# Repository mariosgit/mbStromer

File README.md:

# mbStromer

The Asymmetric Power Supply for Eurorack.

Provides up to 50W, oldschool linear regulator stuff (low noise), for use with a transformer (2x12V 50VA)

With heatsink: 50W
* 12V 3A
* -12V 1A

Without heatsink 25W
* 12V ~1.5A
* -12V ~0.5A

## Status

Under testing, minor fixes pending...

## Mounting

The board can be mounted on a heatsink or directly onto the metal case back, which then becomes the heatsink. You will need 2 silicone pads and 2 Alu/Copper distance peaces 30x40mm. Use the center screw holes to minimize stress on the pcb.

When used without heatsink, put it on distancers so air can circulate around the board which is designed to be disipate a little heat as well.

### Bugs (beta)

* 7912 has no ground conn ! patch it.

## Todo

* Add 5V option ? No one uses it anyway !? Disturbs fend-shui of the layout :-P

## License

#### Attribution-NonCommercial-ShareAlike - CC BY-NC-SA 

```
Attribution — You must give appropriate credit, provide a link to the license, and indicate if changes were made. You may do so in any reasonable manner, but not in any way that suggests the licensor endorses you or your use.

NonCommercial — You may not use the material for commercial purposes.

ShareAlike — If you remix, transform, or build upon the material, you must distribute your contributions under the same license as the original.

No additional restrictions — You may not apply legal terms or technological measures that legally restrict others from doing anything the license permits.
```
[All the legal blabla here](https://creativecommons.org/licenses/by-nc-sa/4.0/legalcode)

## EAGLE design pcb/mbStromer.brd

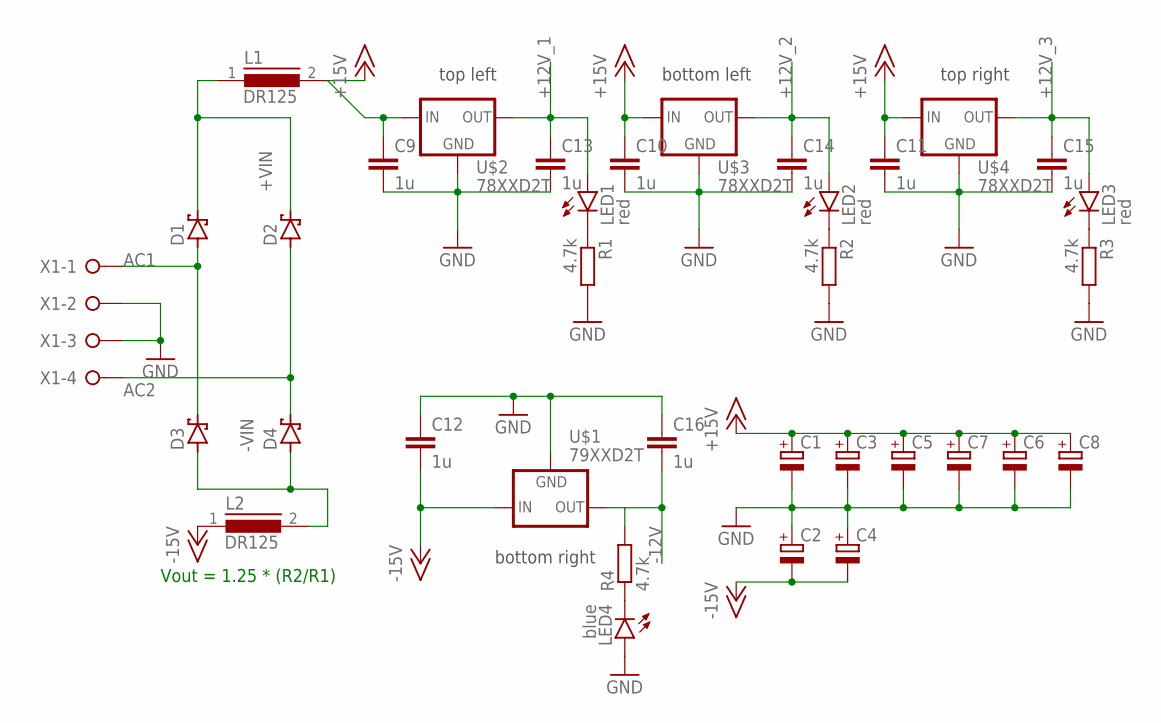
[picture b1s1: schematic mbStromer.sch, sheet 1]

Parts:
C1, C2, C3, C4, C5, C6, C7, C8: CPOL-EU150CLZ-1014; 150CLZ-1014
C9, C10, C11, C12, C13, C14, C15, C16: 1u; C1206K
D1, D2, D3, D4: SCHOTTKY-DIODESMC; SMC
L1, L2: DR125
LED1, LED2, LED3: red; CHIPLED_1206
LED4: blue; CHIPLED_1206
R1, R2, R3, R4: 4.7k; R1206
U$1: 79XXD2T; D2PACK
U$2, U$3, U$4: 78XXD2T; D2PACK
X1: W237-04P; W237-4P

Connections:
+12V_1: C13.1, LED1.A, U$2.3 (OUT); also elsewhere on the board
+12V_2: C14.1, LED2.A, U$3.3 (OUT); also elsewhere on the board
+12V_3: C15.1, LED3.A, U$4.3 (OUT); also elsewhere on the board
+15V: C1.+, C3.+, C5.+, C6.+, C7.+, C8.+, C9.1, C10.1, C11.1, L1.2, U$2.1 (IN), U$3.1 (IN), U$4.1 (IN)
+VIN: D1.C, D2.C, L1.1
-12V: C16.2, R4.2, U$1.3 (OUT); also elsewhere on the board
-15V: C2.-, C4.-, C12.2, L2.1, U$1.2 (IN)
-VIN: D3.A, D4.A, L2.2
AC1: D1.A, D3.C, X1.1
AC2: D2.A, D4.C, X1.4
GND: C1.-, C2.+, C3.-, C4.+, C5.-, C6.-, C7.-, C8.-, C9.2, C10.2, C11.2, C12.1, C13.2, C14.2, C15.2, C16.1, LED4.A, R1.2, R2.2, R3.2, U$1.1 (GND), U$2.2 (GND), U$3.2 (GND), U$4.2 (GND), X1.2, X1.3; also elsewhere on the board
unnamed: LED1.C, R1.1
unnamed: LED2.C, R2.1
unnamed: LED3.C, R3.1
unnamed: LED4.C, R4.1

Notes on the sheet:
Vout = 1.25 * (R2/R1)
top right
top left
bottom left
bottom right

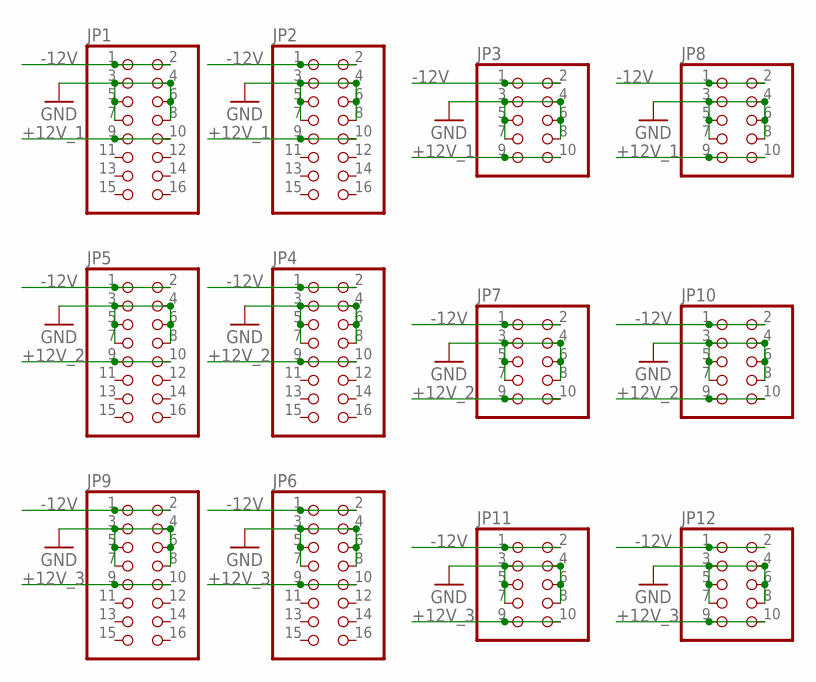
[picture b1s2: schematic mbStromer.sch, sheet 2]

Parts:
JP1, JP2, JP4, JP5, JP6, JP9: PINHD-2X8/90; 2X08/90
JP3, JP7, JP8, JP10, JP11, JP12: PINHD-2X5/90; 2X05/90

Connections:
+12V_1: JP1.9, JP1.10, JP2.9, JP2.10, JP3.9, JP3.10, JP8.9, JP8.10; also elsewhere on the board
+12V_2: JP4.9, JP4.10, JP5.9, JP5.10, JP7.9, JP7.10, JP10.9, JP10.10; also elsewhere on the board
+12V_3: JP6.9, JP6.10, JP9.9, JP9.10, JP11.9, JP11.10, JP12.9, JP12.10; also elsewhere on the board
-12V: JP1.1, JP1.2, JP2.1, JP2.2, JP3.1, JP3.2, JP4.1, JP4.2, JP5.1, JP5.2, JP6.1, JP6.2, JP7.1, JP7.2, JP8.1, JP8.2, JP9.1, JP9.2, JP10.1, JP10.2, JP11.1, JP11.2, JP12.1, JP12.2; also elsewhere on the board
GND: JP1.3, JP1.4, JP1.5, JP1.6, JP1.7, JP1.8, JP2.3, JP2.4, JP2.5, JP2.6, JP2.7, JP2.8, JP3.3, JP3.4, JP3.5, JP3.6, JP3.7, JP3.8, JP4.3, JP4.4, JP4.5, JP4.6, JP4.7, JP4.8, JP5.3, JP5.4, JP5.5, JP5.6, JP5.7, JP5.8, JP6.3, JP6.4, JP6.5, JP6.6, JP6.7, JP6.8, JP7.3, JP7.4, JP7.5, JP7.6, JP7.7, JP7.8, JP8.3, JP8.4, JP8.5, JP8.6, JP8.7, JP8.8, JP9.3, JP9.4, JP9.5, JP9.6, JP9.7, JP9.8, JP10.3, JP10.4, JP10.5, JP10.6, JP10.7, JP10.8, JP11.3, JP11.4, JP11.5, JP11.6, JP11.7, JP11.8, JP12.3, JP12.4, JP12.5, JP12.6, JP12.7, JP12.8; also elsewhere on the board

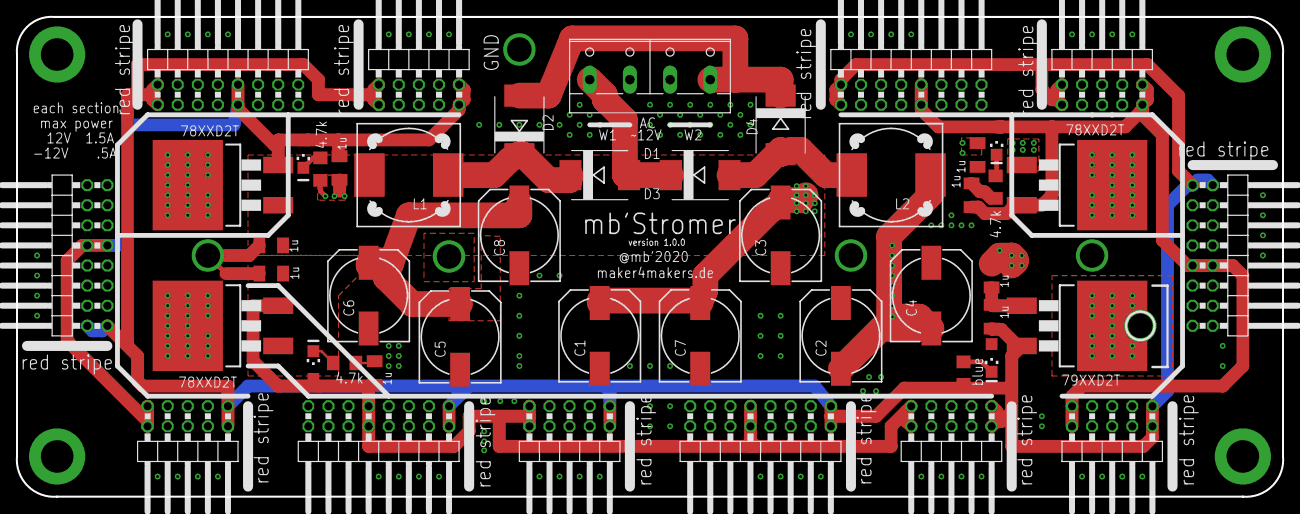
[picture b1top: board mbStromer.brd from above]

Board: 2 copper layers, 160.1 x 60.7 mm, 47 parts (0 on the bottom side), 15 nets.

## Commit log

2020-04-03 fixed typo
2020-04-03 added image
2020-04-03 typo
2020-04-04 3D rendering uuhhh...
2020-04-05 added 3d view
2020-04-19 added schematic pdf
2020-04-19 added BOM csv
2020-04-21 fixed GND@7912, some optimization..
2020-04-21 removed gerber zip
2020-04-24 Fixes and Heatsink recommendations.
2020-04-29 Added License info
